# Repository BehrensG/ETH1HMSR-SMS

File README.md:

<h1>ETH1HMSR-SMS</h1>

ETH1HMSR-SMS is a one-channel data acquisition card based on the HMSR-SMS chip. The communication with a PC is over Ethernet. The card supports LAN eXtensions for Instrumentation (LXI) and RAW TCP and UDP connections.

<h2>DESCRIPTION</h2>

<h3>Device Design</h3>

Key features of the design include:

<ul>
    <li><b>Dimensions</b>: 100 x 45 mm</li>
    <li><b>Power Supply</b>: Operates on a voltage range from 6.5 to 36 VDC (recommended 24 VDC) and includes reverse voltage protection.</li>
    <li><b>Isolation</b>: The HMSR-SMS chip provides isolation protection for the rest of the circuit.</li>
    <li><b>MCU</b>: The STM32H743VITx was selected because of its large internal FLASH and RAM memory, support for Ethernet, and internal 16-bit ADC.</li>
    <li><b>ADC</b>: Internal 16 bit ADC, configured in differential mode.</li>
    <li><b>Software</b>: FreeRTOS with lwip and SCPI parser library.</li>
</ul>

<p align="center">3D model rendition for PCB V1.2.</p>
<p align="center"></img></p>

<p align="center">Below are the images for the PCB V1.0. I made some mistakes, but the botch wires fixed them.</p>

<p align="center"></img></p>
<p align="center"></img></p>
<p align="center"></img></p>

<h3>Input current</h3>

The user can mount different HMSR-SMS models for different measurement ranges, those are :

<table align="center">
    <tr>
        <th>Model</th>
        <th>Nominal current (A)</th>
        <th>Measurement range (A)</th>
        <th>Supported</th>
    </tr>
    <tr>
        <td>HMSR6-SMS</td>
        <td>6</td>
        <td>+/- 15</td>
        <td><font color="green">YES</font></td>
    </tr>
    <tr>
        <td>HMSR8-SMS</td>
        <td>8</td>
        <td>+/- 20</td>
        <td><font color="green">YES</font></td>
    </tr>
    <tr>
        <td>HMSR10-SMS</td>
        <td>10</td>
        <td>+/- 25</td>
        <td><font color="green">YES</font></td>
    </tr>
    <tr>
        <td>HMSR15-SMS</td>
        <td>15</td>
        <td>+/- 37.5</td>
        <td><font color="green">YES</font></td>
    </tr>
    <tr>
        <td>HMSR20-SMS</td>
        <td>20</td>
        <td>+/- 50</td>
        <td><font color="red">NO</font></td>
    </tr>
    <tr>
        <td>HMSR30-SMS</td>
        <td>30</td>
        <td>+/- 75</td>
        <td><font color="red">NO</font></td>
    </tr>
</table>

> [!NOTE]
> The limitations is the input connector (Phoenix Contact 1710072), with nominal current of 32 A. For larger current models, the user need to redesign the PCB.

> [!NOTE]
> The prototype has a HMSR6-SMS. Other current models where not tested.

> [!TIP]
> The HMSR-SMS chip is accurate without any additional calibration.

<h2>Ethernet connection</h2>

The PCB uses Ethernet to communicate with the PC. The features are :

<h3>LAN eXtensions for Instrumentation (LXI)</h3>

LAN eXtensions for Instrumentation (LXI) is a standard for connecting and controlling test and measurement instruments via Ethernet. It allows for easy integration, remote access, and simplified configuration, enhancing the flexibility and scalability of automated test systems.

> [!WARNING]  
> This device does not guarantee full compliance with the LXI standard. The implementation was based on available documentation and observations of an LXI-compliant device.

> [!TIP]
> To use the LXI features the user needs to use a VISA API. In the examples below, the R&S VISA Tools where uses. 

<h4><p align="center">Device autodetect with multicast DNS (mDNS).</p></h4>
<hr>
<p align="center"></img></p>

<h4><p align="center">Support for High Speed LAN Instrument Protocol (HiSLIP).</p></h4>
<hr>
<p align="center"></img></p>

<h4><p align="center">Web interface</p></h4>
<hr>
The device website provides the ability to obtain device information, make measurements, and configure the device. Additionally, it offers a manual with all SCPI commands.

> [!WARNING]
> The website was tested only with Google Chrome  Browser.

<h5><p align="center">Device Home Page</p></h5>
<hr>
<p align="center"></img></p>

<h5><p align="center">Device Network Setup</p></h5>
<hr>
<p align="center"></img></p>

<h5><p align="center">Device Control</p></h5>
<hr>
<p align="center"></img></p>

<h5><p align="center">Device Help</p></h5>
<hr>
<p align="center"></img></p>

<h5><p align="center">Device Service</p></h5>
<hr>
<p align="center"></img></p>

<h3>RAW TCP</h3>
The user can connect to the device directly over the TCP 5025 port.

<h5><p align="center">Using netcat</p></h5>
<hr>
<p align="center"></img></p>

<h5><p align="center">Using putty</p></h5>
<hr>
<p align="center"></img></p>

<h3>RAW UDP</h3>
The user can connect to the device directly via UDP port 5025. Over UDP, there is a very limited set of SCPI commands available for measurement readout.

> [!WARNING]
> The RAW UDP connection is not part of the LXI standard, it is device specific.

<h5><p align="center">Using netcat</p></h5>
<hr>
<p align="center"></img></p>

<h2>Links</h2>

<ul>
    <li><a href="https://www.lem.com/en/hmsr-series" target="_blank">HMSR-SMS</a></li>
    <li><a href="https://www.lxistandard.org/" target="_blank">LAN eXtensions for Instrumentation</a></li>
    <li><a href="https://www.ivifoundation.org/specifications/default.html" target="_blank">High Speed LAN Instrument Protocol (HiSLIP)</a></li>
    <li><a href="https://en.wikipedia.org/wiki/Virtual_instrument_software_architecture" target="_blank">Virtual instrument software architecture (VISA)</a></li>
    <li><a href="https://www.rohde-schwarz.com/us/driver-pages/remote-control/3-visa-and-tools_231388.html" target="_blank">R&S VISA</a></li>
    <li><a href="https://github.com/j123b567/scpi-parser" target="_blank">SCPI Parser</a></li>
   <li><a href="https://github.com/mpaland/printf" target="_blank">A printf / sprintf Implementation for Embedded Systems</a></li>
</ul>

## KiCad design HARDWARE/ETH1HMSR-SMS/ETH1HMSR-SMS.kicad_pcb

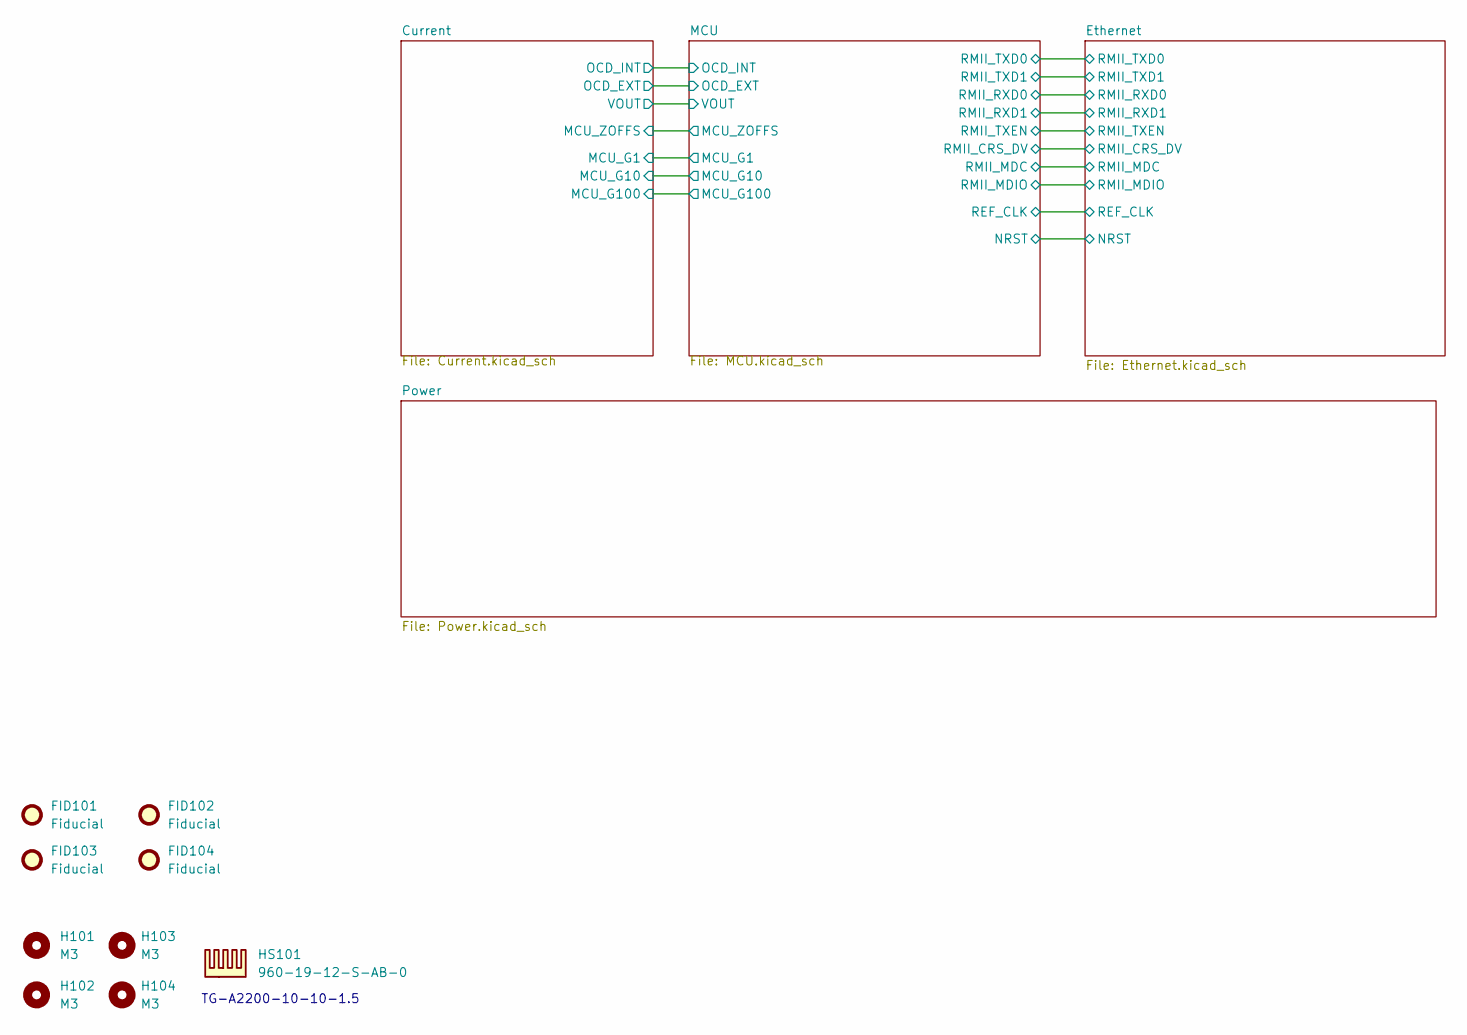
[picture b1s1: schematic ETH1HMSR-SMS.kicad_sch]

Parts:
FID101, FID102, FID103, FID104: Fiducial; Fiducial_1.5mm_Mask3mm
H101, H102: M3; MountingHole_3.2mm_M3_DIN965
H103, H104: M3; MountingHole_3.2mm_M3_DIN965_Pad
HS101: 960-19-12-S-AB-0

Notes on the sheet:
TG-A2200-10-10-1.5

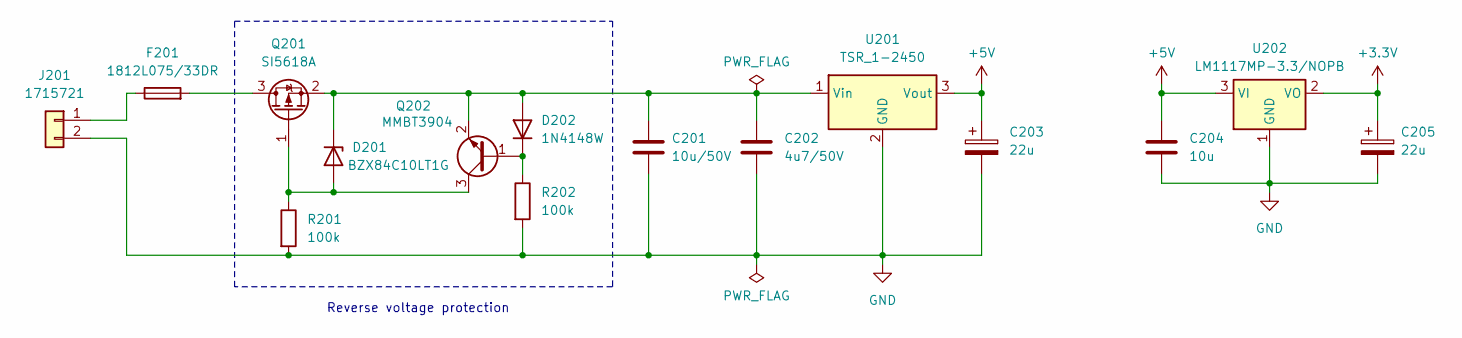
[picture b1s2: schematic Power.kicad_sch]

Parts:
C201: 10u/50V; C_1206_3216Metric_Pad1.33x1.80mm_HandSolder
C202: 4u7/50V; C_1206_3216Metric_Pad1.33x1.80mm_HandSolder
C203, C205: 22u; CP_EIA-3528-21_Kemet-B_Pad1.50x2.35mm_HandSolder
C204: 10u; C_1206_3216Metric_Pad1.33x1.80mm_HandSolder
D201: BZX84C10LT1G; SOT-23
D202: 1N4148W; D_SOD-123
F201: 1812L075/33DR; Fuse_1812_4532Metric_Pad1.30x3.40mm_HandSolder
J201: 1715721; TerminalBlock_Phoenix_MKDS-1,5-2_1x02_P5.00mm_Horizontal
Q201: SI5618A; SOT-23
Q202: MMBT3904; SOT-23
R201, R202: 100k; R_0603_1608Metric_Pad0.98x0.95mm_HandSolder
U201: TSR_1-2450; Converter_DCDC_TRACO_TSR-1_THT
U202: LM1117MP-3.3/NOPB; SOT-223-3_TabPin2

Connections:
+3.3V: C205.1, U202.2 (VO); also elsewhere on the board
+5V: C203.1, C204.1, U201.3 (Vout), U202.3 (VI); also elsewhere on the board
GND: C201.2, C202.2, C203.2, C204.2, C205.2, J201.2, R201.2, R202.2, U201.2 (GND), U202.1 (GND); also elsewhere on the board
unnamed: D201.1 (A), Q201.1 (G), Q202.3 (C), R201.1
unnamed: C201.1, C202.1, D201.3 (K), D202.2 (A), Q201.2 (S), Q202.2 (E), U201.1 (Vin)
unnamed: D202.1 (K), Q202.1 (B), R202.1
unnamed: F201.1, J201.1
unnamed: F201.2, Q201.3 (D)

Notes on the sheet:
Reverse voltage protection

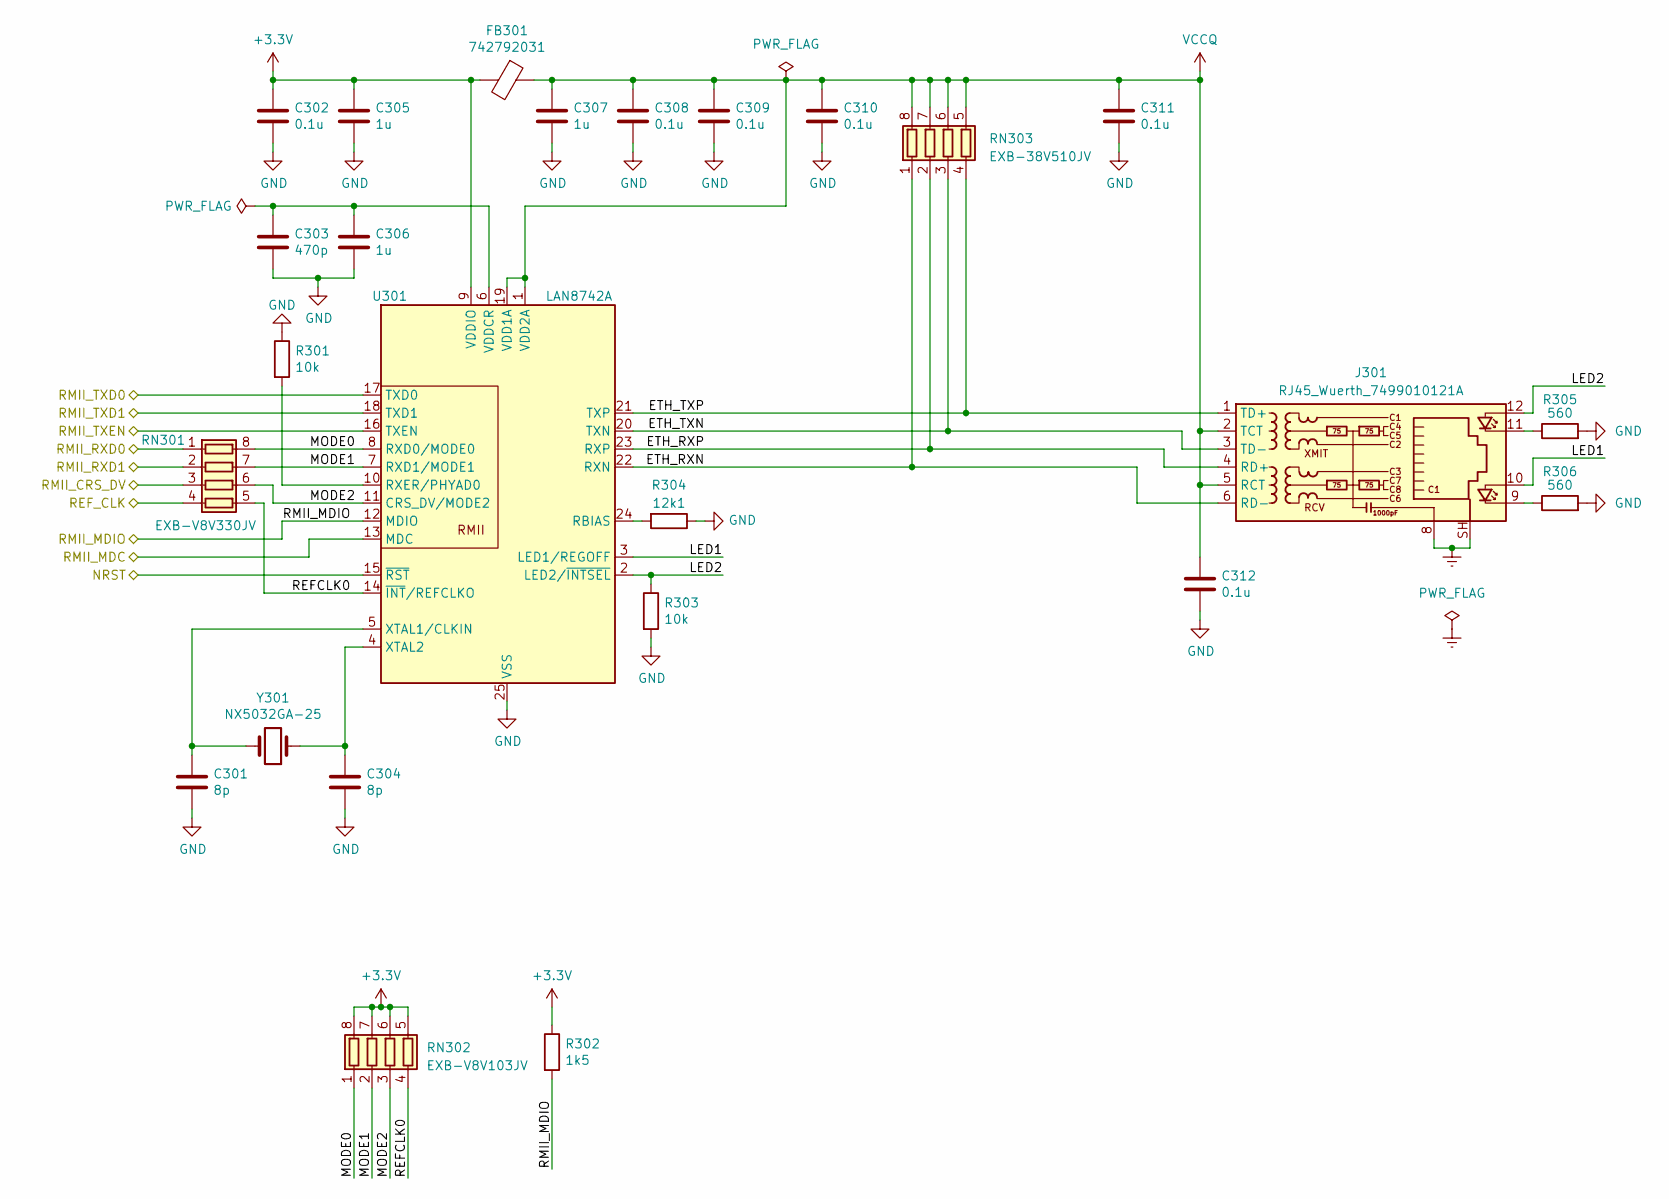
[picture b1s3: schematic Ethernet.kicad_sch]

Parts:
C301, C304: 8p; C_0603_1608Metric_Pad1.08x0.95mm_HandSolder
C302, C308, C309, C310, C311, C312: 0.1u; C_0603_1608Metric_Pad1.08x0.95mm_HandSolder
C303: 470p; C_0603_1608Metric_Pad1.08x0.95mm_HandSolder
C305, C306, C307: 1u; C_0603_1608Metric_Pad1.08x0.95mm_HandSolder
FB301: 742792031; L_0805_2012Metric_Pad1.05x1.20mm_HandSolder
J301: RJ45_Wuerth_7499010121A; RJ45_Wuerth_7499010121A_Horizontal
R301, R303: 10k; R_0603_1608Metric_Pad0.98x0.95mm_HandSolder
R302: 1k5; R_0603_1608Metric_Pad0.98x0.95mm_HandSolder
R304: 12k1; R_0603_1608Metric_Pad0.98x0.95mm_HandSolder
R305, R306: 560; R_0603_1608Metric_Pad0.98x0.95mm_HandSolder
RN301: EXB-V8V330JV; R_Array_Concave_4x0603
RN302: EXB-V8V103JV; R_Array_Concave_4x0603
RN303: EXB-38V510JV; R_Array_Concave_4x0603
U301: LAN8742A; VQFN-24-1EP_4x4mm_P0.5mm_EP2.5x2.5mm_ThermalVias
Y301: NX5032GA-25; NX5032GA

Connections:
+3.3V: C302.1, C305.1, FB301.2, R302.1, RN302.5 (R4.2), RN302.6 (R3.2), RN302.7 (R2.2), RN302.8 (R1.2), U301.9 (VDDIO); also elsewhere on the board
/Ethernet/ETH_RXN: J301.6 (RD-), RN303.1 (R1.1), U301.22 (RXN)
/Ethernet/ETH_RXP: J301.4 (RD+), RN303.2 (R2.1), U301.23 (RXP)
/Ethernet/ETH_TXN: J301.3 (TD-), RN303.3 (R3.1), U301.20 (TXN)
/Ethernet/ETH_TXP: J301.1 (TD+), RN303.4 (R4.1), U301.21 (TXP)
/Ethernet/LED1: J301.10, U301.3 (LED1/REGOFF)
/Ethernet/LED2: J301.12, R303.1, U301.2 (LED2/~INTSEL)
/Ethernet/MODE0: RN301.8 (R1.2), RN302.1 (R1.1), U301.8 (RXD0/MODE0)
/Ethernet/MODE1: RN301.7 (R2.2), RN302.2 (R2.1), U301.7 (RXD1/MODE1)
/Ethernet/MODE2: RN301.6 (R3.2), RN302.3 (R3.1), U301.11 (CRS_DV/MODE2)
/Ethernet/REFCLK0: RN301.5 (R4.2), RN302.4 (R4.1), U301.14 (~INT/REFCLKO)
/Ethernet/REF_CLK: RN301.4 (R4.1); also elsewhere on the board
/Ethernet/RMII_CRS_DV: RN301.3 (R3.1); also elsewhere on the board
/Ethernet/RMII_MDC: U301.13 (MDC); also elsewhere on the board
/Ethernet/RMII_MDIO: R302.2, U301.12 (MDIO); also elsewhere on the board
/Ethernet/RMII_RXD0: RN301.1 (R1.1); also elsewhere on the board
/Ethernet/RMII_RXD1: RN301.2 (R2.1); also elsewhere on the board
/Ethernet/RMII_TXD0: U301.17 (TXD0); also elsewhere on the board
/Ethernet/RMII_TXD1: U301.18 (TXD1); also elsewhere on the board
/Ethernet/RMII_TXEN: U301.16 (TXEN); also elsewhere on the board
/MCU/NRST: U301.15 (~RST); also elsewhere on the board
Earth: J301.8, J301.SH
GND: C301.2, C302.2, C303.2, C304.2, C305.2, C306.2, C307.2, C308.2, C309.2, C310.2, C311.2, C312.2, R301.1, R303.2, R304.1, R305.2, R306.2, U301.25 (VSS); also elsewhere on the board
unnamed: J301.9, R306.1
unnamed: J301.11, R305.1
unnamed: R304.2, U301.24 (RBIAS)
unnamed: R301.2, U301.10 (RXER/PHYAD0)
unnamed: C303.1, C306.1, U301.6 (VDDCR)
unnamed: C301.1, U301.5 (XTAL1/CLKIN), Y301.2
unnamed: C304.1, U301.4 (XTAL2), Y301.1
VCCQ: C307.1, C308.1, C309.1, C310.1, C311.1, C312.1, FB301.1, J301.2 (TCT), J301.5 (RCT), RN303.5 (R4.2), RN303.6 (R3.2), RN303.7 (R2.2), RN303.8 (R1.2), U301.1 (VDD2A), U301.19 (VDD1A)

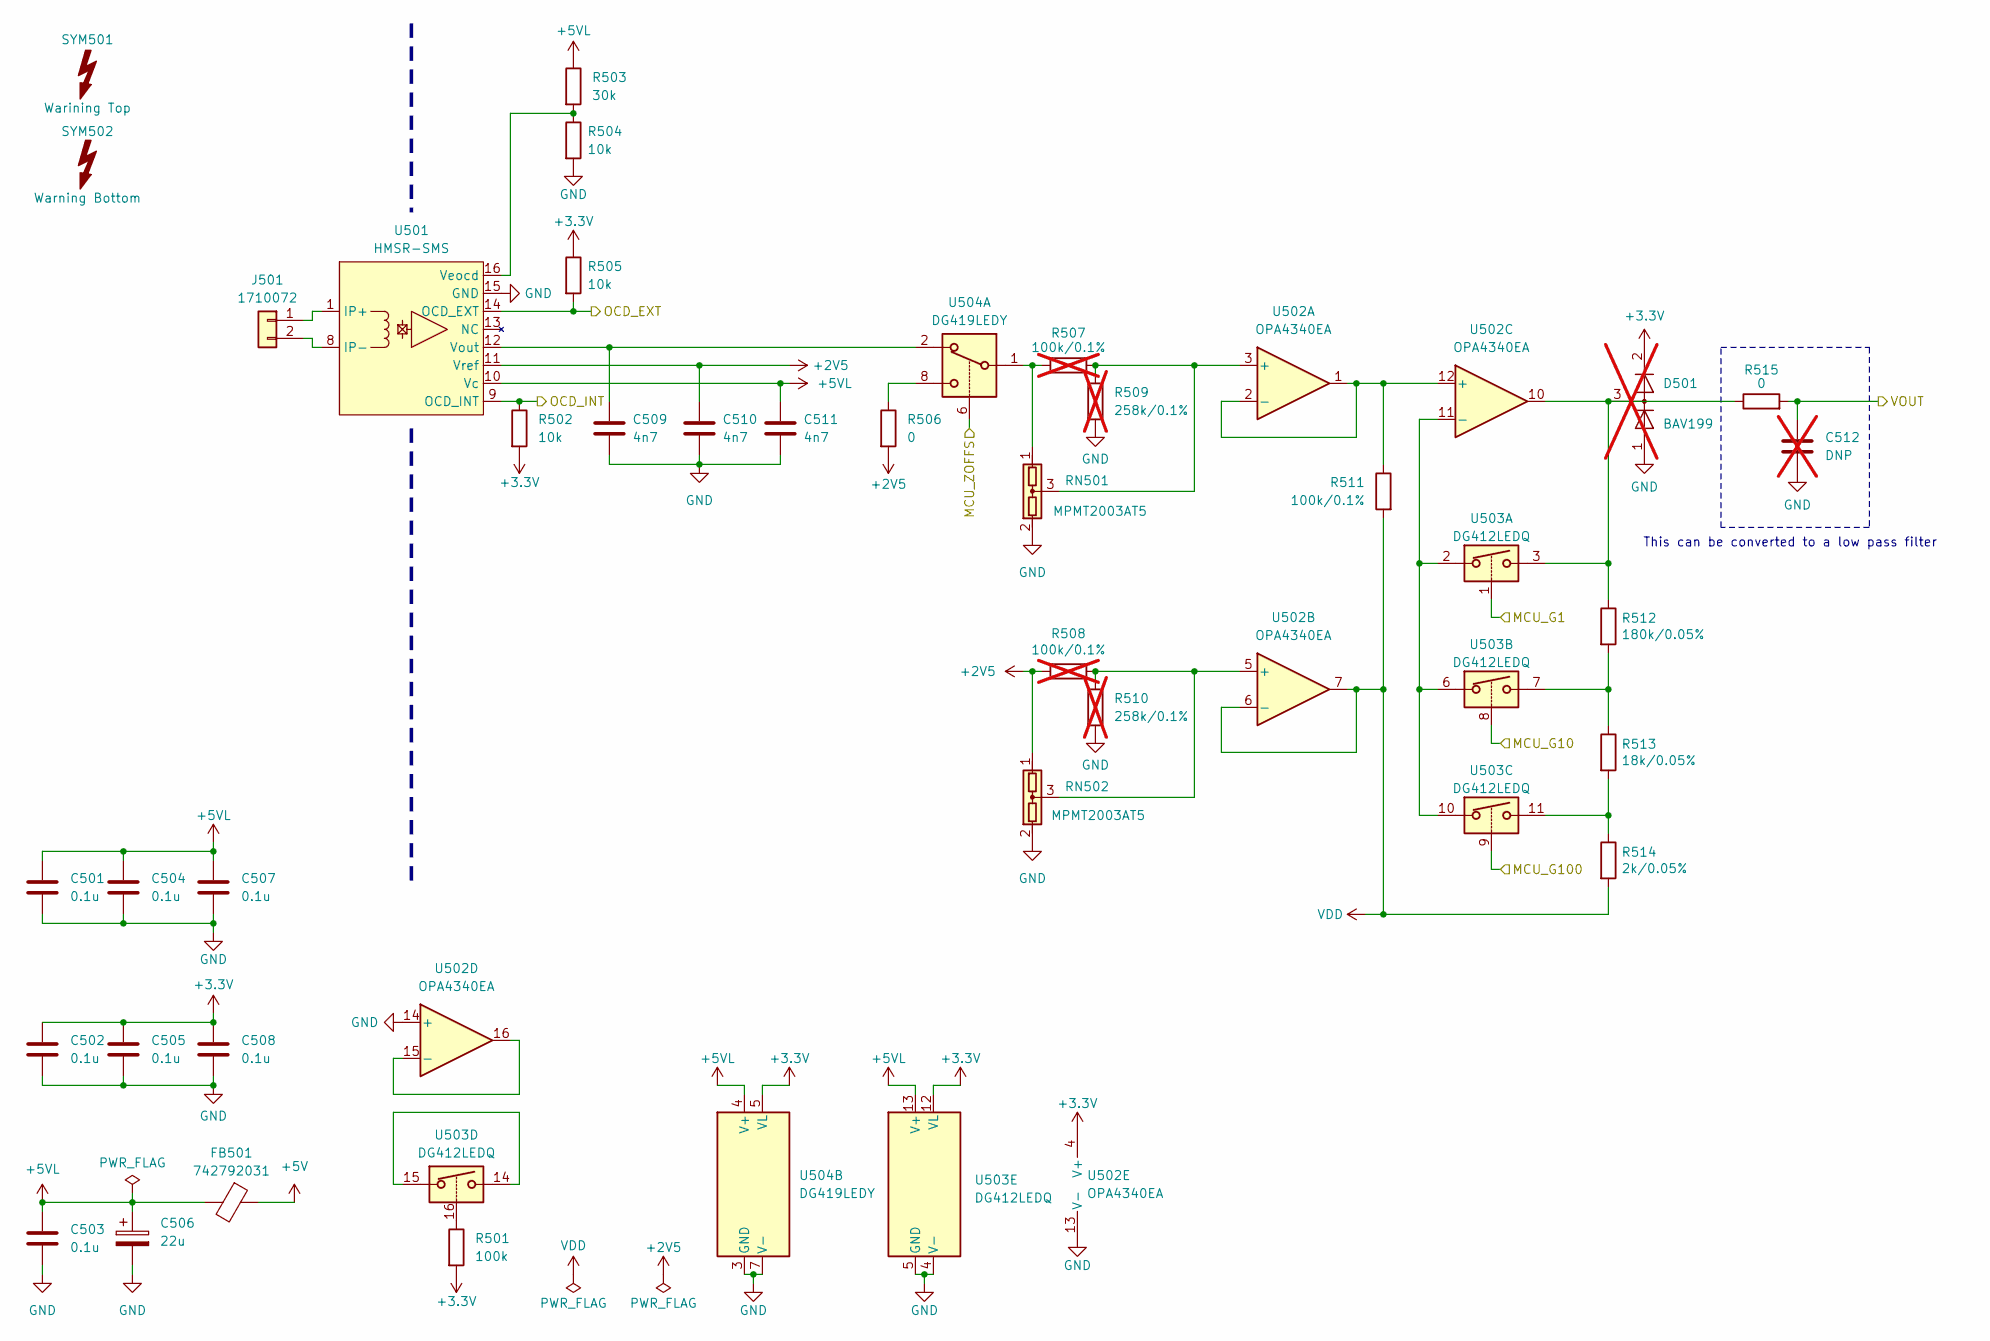
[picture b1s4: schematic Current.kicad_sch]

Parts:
C501, C502, C503, C504, C505, C507, C508: 0.1u; C_0603_1608Metric_Pad1.08x0.95mm_HandSolder
C506: 22u; CP_EIA-3528-21_Kemet-B_Pad1.50x2.35mm_HandSolder
C509, C510, C511: 4n7; C_0603_1608Metric_Pad1.08x0.95mm_HandSolder
C512: DNP; C_0603_1608Metric_Pad1.08x0.95mm_HandSolder; not fitted
D501: BAV199; SOT-23; not fitted
FB501: 742792031; L_0805_2012Metric_Pad1.05x1.20mm_HandSolder
J501: 1710072
R501: 100k; R_0603_1608Metric_Pad0.98x0.95mm_HandSolder
R502, R504, R505: 10k; R_0603_1608Metric_Pad0.98x0.95mm_HandSolder
R503: 30k; R_0603_1608Metric_Pad0.98x0.95mm_HandSolder
R506, R515: 0; R_0603_1608Metric_Pad0.98x0.95mm_HandSolder
R507, R508: 100k/0.1%; R_0603_1608Metric_Pad0.98x0.95mm_HandSolder; not fitted
R509, R510: 258k/0.1%; R_0603_1608Metric_Pad0.98x0.95mm_HandSolder; not fitted
R511: 100k/0.1%; R_0603_1608Metric_Pad0.98x0.95mm_HandSolder
R512: 180k/0.05%; R_0603_1608Metric_Pad0.98x0.95mm_HandSolder
R513: 18k/0.05%; R_0603_1608Metric_Pad0.98x0.95mm_HandSolder
R514: 2k/0.05%; R_0603_1608Metric_Pad0.98x0.95mm_HandSolder
RN501, RN502: MPMT2003AT5; SOT-23
SYM501: Warining Top; Symbol_Attention_Triangle_8x7mm_Copper
SYM502: Warning Bottom; Symbol_Attention_Triangle_8x7mm_Copper
U501: HMSR-SMS
U502: OPA4340EA; SSOP-16_3.9x4.9mm_P0.635mm
U503: DG412LEDQ; TSSOP-16_4.4x5mm_P0.65mm
U504: DG419LEDY; SOIC-8_3.9x4.9mm_P1.27mm

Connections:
+2V5: C510.1, R506.2, R508.1, RN502.1, U501.11 (Vref)
+3.3V: C502.1, C505.1, C508.1, D501.2 (A), R501.2, R502.2, R505.1, U502.4 (V+), U503.12 (VL), U504.5 (VL); also elsewhere on the board
+5V: FB501.1; also elsewhere on the board
+5VL: C501.1, C503.1, C504.1, C506.1, C507.1, C511.1, FB501.2, R503.1, U501.10 (Vc), U503.13 (V+), U504.4 (V+); also elsewhere on the board
/Current/MCU_G1: U503.1; also elsewhere on the board
/Current/MCU_G10: U503.8; also elsewhere on the board
/Current/MCU_G100: U503.9; also elsewhere on the board
/Current/MCU_ZOFFS: U504.6; also elsewhere on the board
/Current/OCD_EXT: R505.2, U501.14 (OCD_EXT); also elsewhere on the board
/Current/OCD_INT: R502.1, U501.9 (OCD_INT); also elsewhere on the board
/Current/VOUT: C512.1, R515.2; also elsewhere on the board
GND: C501.2, C502.2, C503.2, C504.2, C505.2, C506.2, C507.2, C508.2, C509.2, C510.2, C511.2, C512.2, D501.1 (K), R504.2, R509.2, R510.2, RN501.2, RN502.2, U501.15 (GND), U502.13 (V-), U502.14 (+), U503.4 (V-), U503.5 (GND), U504.3 (GND), U504.7 (V-); also elsewhere on the board
unnamed: D501.3 (K), R512.1, R515.1, U502.10, U503.3
unnamed: J501.1, U501.1 (IP+)
unnamed: J501.2, U501.8 (IP-)
unnamed: R501.1, U503.16
unnamed: R506.1, U504.8
unnamed: R507.1, RN501.1, U504.1
unnamed: R512.2, R513.1, U503.7
unnamed: R513.2, R514.1, U503.11
unnamed: R503.2, R504.1, U501.16 (Veocd)
unnamed: C509.1, U501.12 (Vout), U504.2
unnamed: R507.2, R509.1, RN501.3, U502.3 (+)
unnamed: R511.1, U502.1, U502.2 (-), U502.12 (+)
unnamed: R508.2, R510.1, RN502.3, U502.5 (+)
unnamed: U502.11 (-), U503.2, U503.6, U503.10
unnamed: U502.15 (-), U502.16
unnamed: U503.14, U503.15
VDD: R511.2, R514.2, U502.6 (-), U502.7; also elsewhere on the board

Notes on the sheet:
This can be converted to a low pass filter

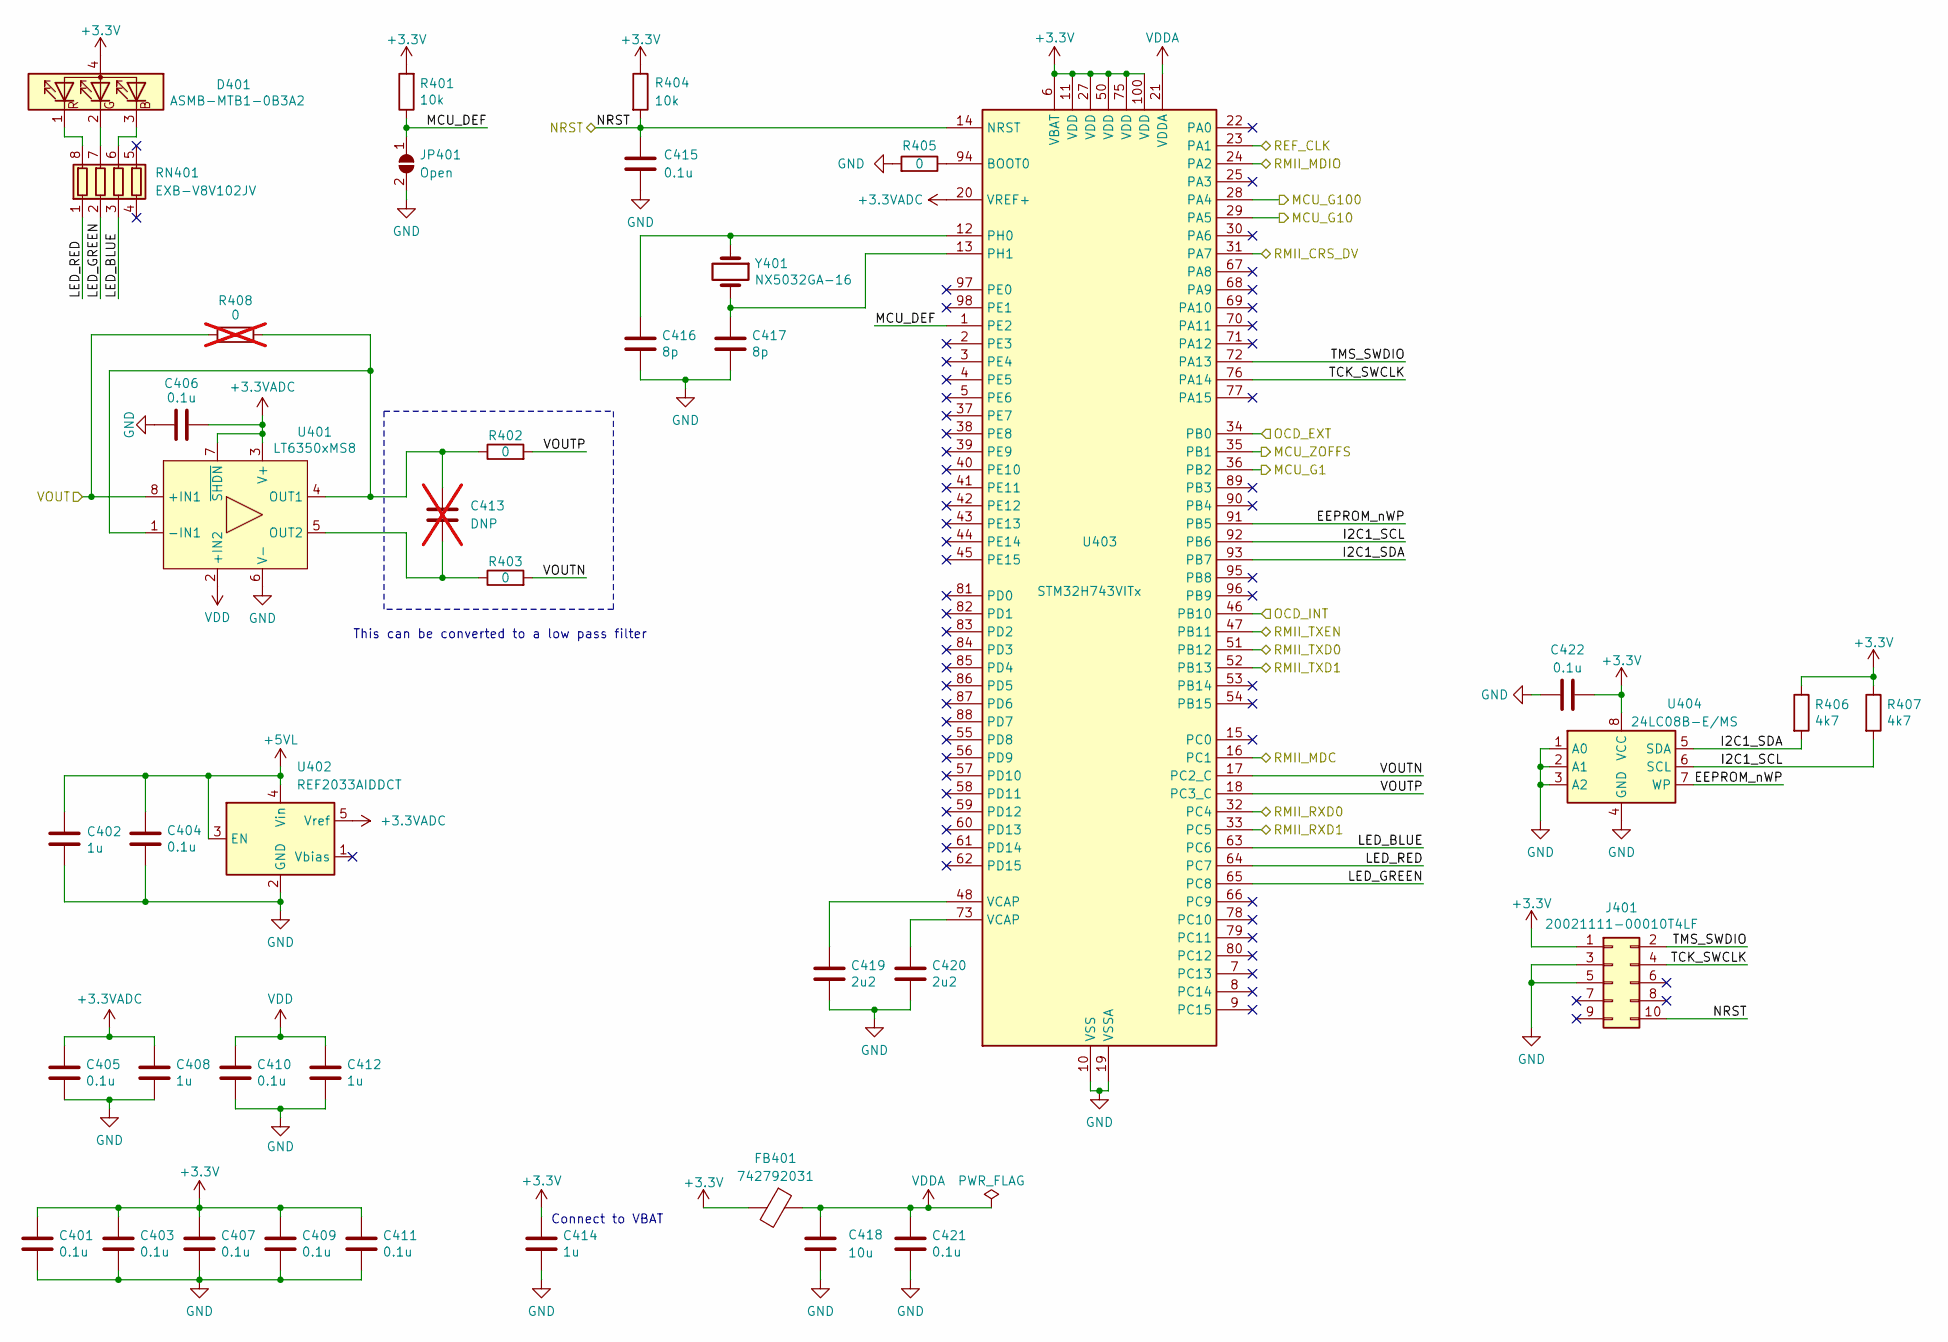
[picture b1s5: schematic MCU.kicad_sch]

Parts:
C401, C403, C404, C405, C406, C407, C409, C410, C411, C415, C421, C422: 0.1u; C_0603_1608Metric_Pad1.08x0.95mm_HandSolder
C402, C408, C412, C414: 1u; C_0603_1608Metric_Pad1.08x0.95mm_HandSolder
C413: DNP; C_0603_1608Metric_Pad1.08x0.95mm_HandSolder; not fitted
C416, C417: 8p; C_0603_1608Metric_Pad1.08x0.95mm_HandSolder
C418: 10u; C_0603_1608Metric_Pad1.08x0.95mm_HandSolder
C419, C420: 2u2; C_0603_1608Metric_Pad1.08x0.95mm_HandSolder
D401: ASMB-MTB1-0B3A2; LED_Avago_PLCC4_3.2x2.8mm_CW
FB401: 742792031; L_0805_2012Metric_Pad1.05x1.20mm_HandSolder
J401: 20021111-00010T4LF; PinHeader_2x05_P1.27mm_Vertical
JP401: Open; SolderJumper-2_P1.3mm_Open_Pad1.0x1.5mm
R401, R404: 10k; R_0603_1608Metric_Pad0.98x0.95mm_HandSolder
R402, R403, R405: 0; R_0603_1608Metric_Pad0.98x0.95mm_HandSolder
R406, R407: 4k7; R_0603_1608Metric_Pad0.98x0.95mm_HandSolder
R408: 0; R_0603_1608Metric_Pad0.98x0.95mm_HandSolder; not fitted
RN401: EXB-V8V102JV; R_Array_Concave_4x0603
U401: LT6350xMS8; MSOP-8_3x3mm_P0.65mm
U402: REF2033AIDDCT; SOT-23-5_HandSoldering
U403: STM32H743VITx; LQFP-100_14x14mm_P0.5mm
U404: 24LC08B-E/MS; MSOP-8_3x3mm_P0.65mm
Y401: NX5032GA-16; NX5032GA

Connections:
+3.3V: C401.1, C403.1, C407.1, C409.1, C411.1, C414.1, C422.2, D401.4 (A), FB401.2, J401.1, R401.2, R404.1, R406.1, R407.1, U403.6 (VBAT), U403.11 (VDD), U403.27 (VDD), U403.50 (VDD), U403.75 (VDD), U403.100 (VDD), U404.8 (VCC); also elsewhere on the board
+3.3VADC: C405.1, C406.1, C408.1, U401.3 (V+), U401.7 (~SHDN), U402.5 (Vref), U403.20 (VREF+)
+5VL: C402.1, C404.1, U402.3 (EN), U402.4 (Vin); also elsewhere on the board
/Current/MCU_G1: U403.36 (PB2); also elsewhere on the board
/Current/MCU_G10: U403.29 (PA5); also elsewhere on the board
/Current/MCU_G100: U403.28 (PA4); also elsewhere on the board
/Current/MCU_ZOFFS: U403.35 (PB1); also elsewhere on the board
/Current/OCD_EXT: U403.34 (PB0); also elsewhere on the board
/Current/OCD_INT: U403.46 (PB10); also elsewhere on the board
/Current/VOUT: R408.1, U401.8 (+IN1); also elsewhere on the board
/Ethernet/REF_CLK: U403.23 (PA1); also elsewhere on the board
/Ethernet/RMII_CRS_DV: U403.31 (PA7); also elsewhere on the board
/Ethernet/RMII_MDC: U403.16 (PC1); also elsewhere on the board
/Ethernet/RMII_MDIO: U403.24 (PA2); also elsewhere on the board
/Ethernet/RMII_RXD0: U403.32 (PC4); also elsewhere on the board
/Ethernet/RMII_RXD1: U403.33 (PC5); also elsewhere on the board
/Ethernet/RMII_TXD0: U403.51 (PB12); also elsewhere on the board
/Ethernet/RMII_TXD1: U403.52 (PB13); also elsewhere on the board
/Ethernet/RMII_TXEN: U403.47 (PB11); also elsewhere on the board
/MCU/EEPROM_nWP: U403.91 (PB5), U404.7 (WP)
/MCU/I2C1_SCL: R407.2, U403.92 (PB6), U404.6 (SCL)
/MCU/I2C1_SDA: R406.2, U403.93 (PB7), U404.5 (SDA)
/MCU/LED_BLUE: RN401.3 (R3.1), U403.63 (PC6)
/MCU/LED_GREEN: RN401.2 (R2.1), U403.65 (PC8)
/MCU/LED_RED: RN401.1 (R1.1), U403.64 (PC7)
/MCU/MCU_DEF: JP401.1 (A), R401.1, U403.1 (PE2)
/MCU/NRST: C415.1, J401.10, R404.2, U403.14 (NRST); also elsewhere on the board
/MCU/TCK_SWCLK: J401.4, U403.76 (PA14)
/MCU/TMS_SWDIO: J401.2, U403.72 (PA13)
/MCU/VOUTN: R403.2, U403.17 (PC2_C)
/MCU/VOUTP: R402.2, U403.18 (PC3_C)
GND: C401.2, C402.2, C403.2, C404.2, C405.2, C406.2, C407.2, C408.2, C409.2, C410.2, C411.2, C412.2, C414.2, C415.2, C416.2, C417.2, C418.2, C419.2, C420.2, C421.2, C422.1, J401.3, J401.5, JP401.2 (B), R405.2, U401.6 (V-), U402.2 (GND), U403.10 (VSS), U403.19 (VSSA), U403.26 (VSS), U403.49 (VSS), U403.74 (VSS), U403.99 (VSS), U404.1 (A0), U404.2 (A1), U404.3 (A2), U404.4 (GND); also elsewhere on the board
unnamed: C419.1, U403.48 (VCAP)
unnamed: C420.1, U403.73 (VCAP)
unnamed: D401.3 (BK), RN401.6 (R3.2)
unnamed: D401.2 (GK), RN401.7 (R2.2)
unnamed: D401.1 (RK), RN401.8 (R1.2)
unnamed: C413.1, R402.1, R408.2, U401.1 (-IN1), U401.4 (OUT1)
unnamed: C413.2, R403.1, U401.5 (OUT2)
unnamed: R405.1, U403.94 (BOOT0)
unnamed: C416.1, U403.12 (PH0), Y401.1
unnamed: C417.1, U403.13 (PH1), Y401.2
VDD: C410.1, C412.1, U401.2 (+IN2); also elsewhere on the board
VDDA: C418.1, C421.1, FB401.1, U403.21 (VDDA)

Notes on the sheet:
This can be converted to a low pass filter
Connect to VBAT

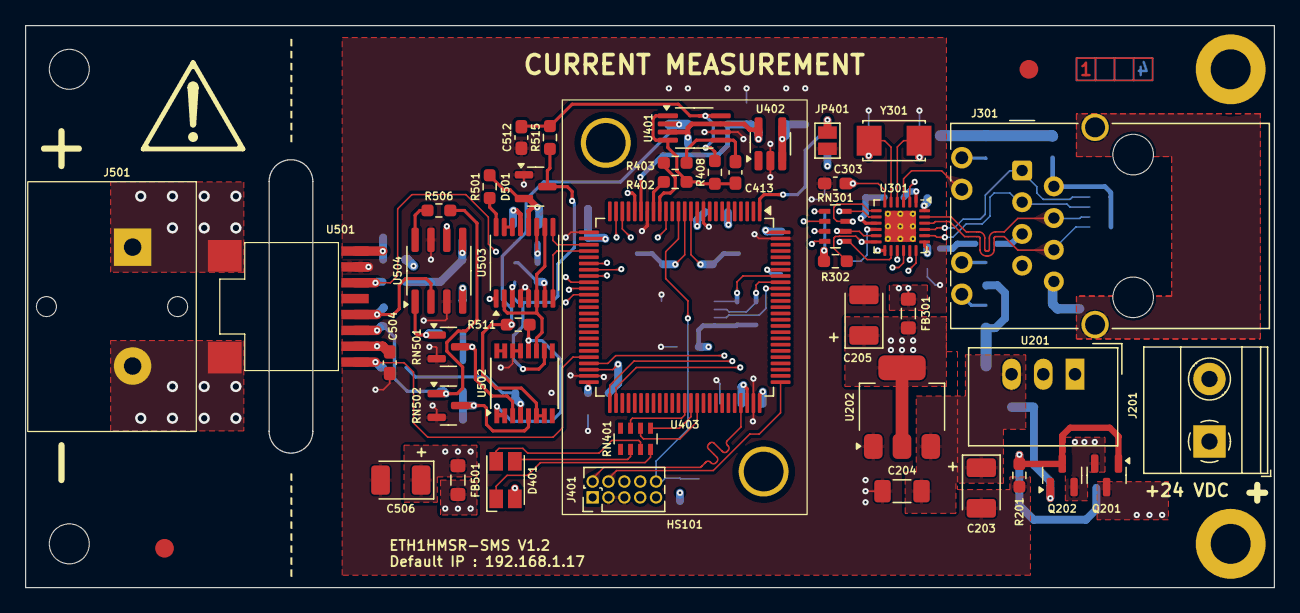
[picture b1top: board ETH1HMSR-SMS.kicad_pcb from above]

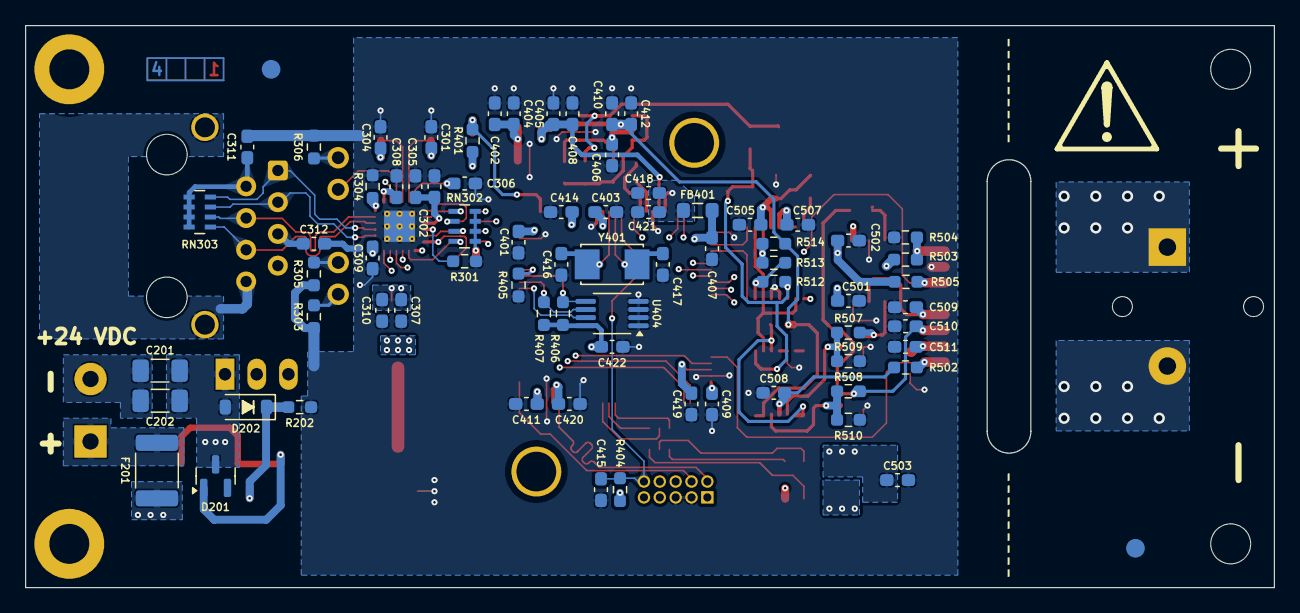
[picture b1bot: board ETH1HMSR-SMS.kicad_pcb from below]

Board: 4 copper layers, 100.0 x 45.0 mm, 127 parts (76 on the bottom side), 86 nets.

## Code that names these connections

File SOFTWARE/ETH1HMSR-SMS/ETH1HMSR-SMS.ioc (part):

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Mcu.Name=STM32H743VITx
Mcu.Package=LQFP100
Mcu.UserName=STM32H743VITx
PA1.GPIOParameters=GPIO_Speed
PA1.GPIO_Speed=GPIO_SPEED_FREQ_VERY_HIGH
PA1.Mode=RMII
PA1.Signal=ETH_REF_CLK
PA2.GPIOParameters=GPIO_Speed
PA2.GPIO_Speed=GPIO_SPEED_FREQ_VERY_HIGH
PA2.Mode=RMII
PA2.Signal=ETH_MDIO
PA4.GPIOParameters=GPIO_Speed,PinState,GPIO_Label
PA4.GPIO_Label=MCU_G100
PA4.GPIO_Speed=GPIO_SPEED_FREQ_HIGH
PA4.PinState=GPIO_PIN_RESET
PA4.Signal=GPIO_Output
PA5.GPIOParameters=GPIO_Speed,PinState,GPIO_Label
PA5.GPIO_Label=MCU_G10
PA5.GPIO_Speed=GPIO_SPEED_FREQ_HIGH
PA5.PinState=GPIO_PIN_RESET
PA5.Signal=GPIO_Output
PA7.GPIOParameters=GPIO_Speed
PA7.GPIO_Speed=GPIO_SPEED_FREQ_VERY_HIGH
PA7.Mode=RMII
PA7.Signal=ETH_CRS_DV
PB0.GPIOParameters=GPIO_Label
PB0.GPIO_Label=OCD_EXT
PB0.Signal=GPXTI0
PB1.GPIOParameters=GPIO_Speed,GPIO_Label
PB1.GPIO_Label=MCU_ZOFFS
PB1.GPIO_Speed=GPIO_SPEED_FREQ_HIGH
PB1.Signal=GPIO_Output
PB10.GPIOParameters=GPIO_Label
PB10.GPIO_Label=OCD_INT
PB10.Signal=GPXTI10
PB11.GPIOParameters=GPIO_Speed
PB11.GPIO_Speed=GPIO_SPEED_FREQ_VERY_HIGH
PB11.Mode=RMII
PB11.Signal=ETH_TX_EN
PB12.GPIOParameters=GPIO_Speed
PB12.GPIO_Speed=GPIO_SPEED_FREQ_VERY_HIGH
PB12.Mode=RMII
PB12.Signal=ETH_TXD0
PB13.GPIOParameters=GPIO_Speed
PB13.GPIO_Speed=GPIO_SPEED_FREQ_VERY_HIGH
PB13.Mode=RMII
PB13.Signal=ETH_TXD1
PB2.GPIOParameters=GPIO_Speed,PinState,GPIO_Label
PB2.GPIO_Label=MCU_G1
PB2.GPIO_Speed=GPIO_SPEED_FREQ_HIGH
PB2.PinState=GPIO_PIN_SET
PB2.Signal=GPIO_Output
PB5.GPIOParameters=GPIO_Speed,PinState,GPIO_Label
PB5.GPIO_Label=EEPROM_nWP
PB5.GPIO_Speed=GPIO_SPEED_FREQ_HIGH
PB5.PinState=GPIO_PIN_SET
PB5.Signal=GPIO_Output
PB6.Mode=I2C
PB6.Signal=I2C1_SCL
PB7.Mode=I2C
PB7.Signal=I2C1_SDA
PC1.GPIOParameters=GPIO_Speed
PC1.GPIO_Speed=GPIO_SPEED_FREQ_LOW
PC1.Mode=RMII
PC1.Signal=ETH_MDC
PC2_C.Mode=IN1-Differential
PC2_C.Signal=ADC3_INN1
PC3_C.Mode=IN1-Differential
PC3_C.Signal=ADC3_INP1
PC4.GPIOParameters=GPIO_Speed
PC4.GPIO_Speed=GPIO_SPEED_FREQ_VERY_HIGH
PC4.Mode=RMII
PC4.Signal=ETH_RXD0
PC5.GPIOParameters=GPIO_Speed
PC5.GPIO_Speed=GPIO_SPEED_FREQ_VERY_HIGH
PC5.Mode=RMII
PC5.Signal=ETH_RXD1
PC6.GPIOParameters=PinState,GPIO_Label
PC6.GPIO_Label=LED_BLUE
PC6.PinState=GPIO_PIN_SET
PC6.Signal=GPIO_Output
PC7.GPIOParameters=PinState,GPIO_Label
PC7.GPIO_Label=LED_RED
PC7.PinState=GPIO_PIN_SET
PC7.Signal=GPIO_Output
PC8.GPIOParameters=PinState,GPIO_Label
PC8.GPIO_Label=LED_GREEN
PC8.PinState=GPIO_PIN_SET
PC8.Signal=GPIO_Output
PE2.GPIOParameters=GPIO_Label
PE2.GPIO_Label=MCU_DEFAULT
PE2.Signal=GPIO_Input
PH0-OSC_IN\ (PH0).Mode=HSE-External-Oscillator
PH0-OSC_IN\ (PH0).Signal=RCC_OSC_IN
PH1-OSC_OUT\ (PH1).Mode=HSE-External-Oscillator
PH1-OSC_OUT\ (PH1).Signal=RCC_OSC_OUT
RCC.HSE_VALUE=16000000
RCC.SYSCLKFreq_VALUE=480000000
RCC.SYSCLKSource=RCC_SYSCLKSOURCE_PLLCLK
board=custom

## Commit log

2024-03-14 HW and SW design
2024-03-15 SW and HW development
2024-03-15 Updated to Kicad 8
2024-03-16 PCB design
2024-03-17 Development
2024-07-02 Init
2024-07-02 Small changes and cleanup
2024-07-02 Bug fixes
2024-07-06 Readme.md file design
2024-07-06 README.md
2024-07-06 Changed web_Service.png
2024-07-12 BOM updated
2024-07-17 Fix in help.html
2024-07-18 Bug fixes.
2024-07-18 Bug fix
2024-08-13 Added new SCPI commands. Updated the help.html. Modified the control.html and added function in HTTP/Src/HTTP_Control.c.
2024-08-14 Small improvements.
2024-11-14 service.html : bug fix in nominal current selection.
